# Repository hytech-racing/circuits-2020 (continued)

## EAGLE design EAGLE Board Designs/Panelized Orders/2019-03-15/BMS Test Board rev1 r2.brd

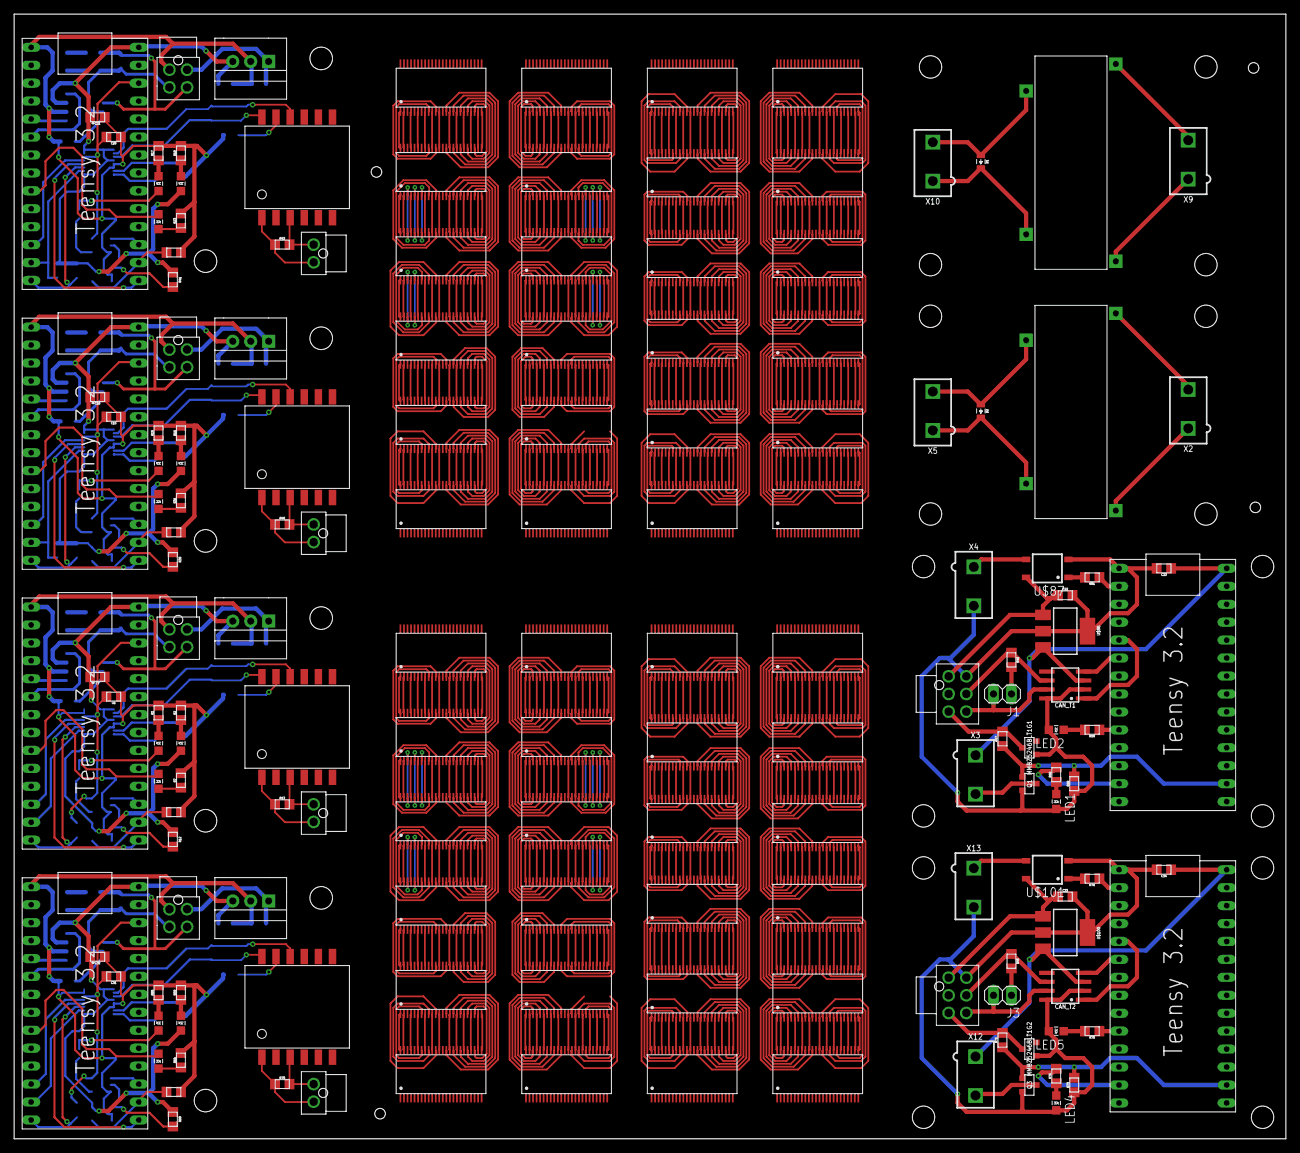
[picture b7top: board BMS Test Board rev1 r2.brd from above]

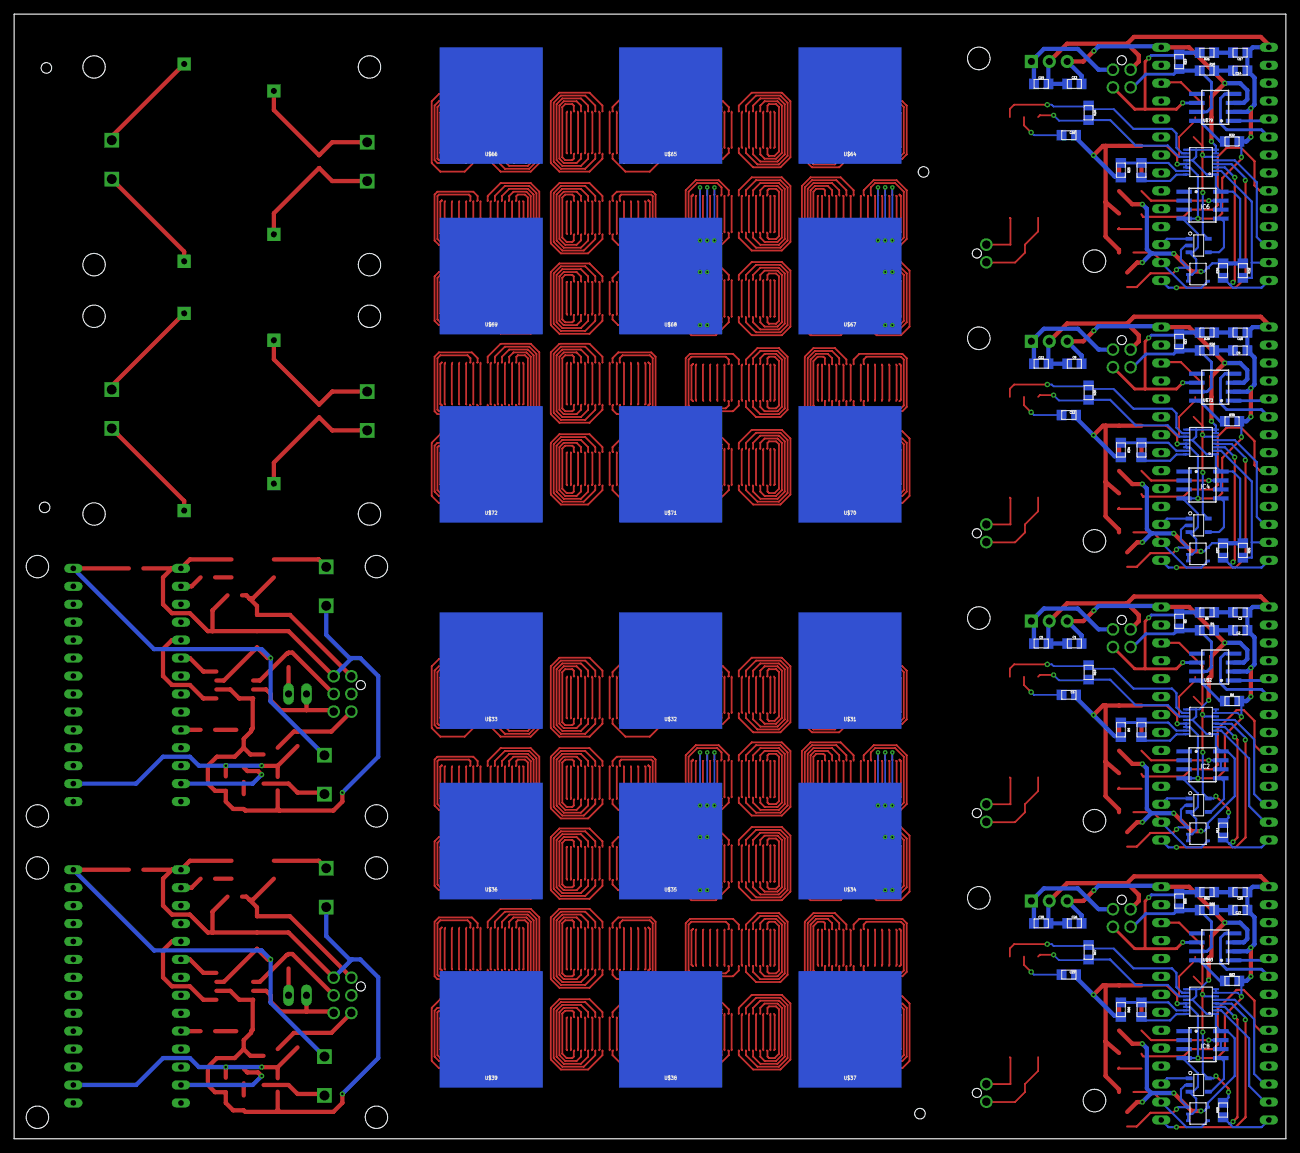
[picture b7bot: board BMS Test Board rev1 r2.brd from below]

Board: 2 copper layers, 180.1 x 159.3 mm, 252 parts (92 on the bottom side), 1128 nets.

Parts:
BMS-OK, BMS-OK1, BMS-OK2, BMS-OK3: GREEN; LED-805
C1, C5, C8, C12, C13, C19, C26, C30: 10uF; 0805
C2, C3, C9, C10, C14, C17, C27, C28: 560pF; 0805
C4, C11, C18, C29: 27pF; 0805
C6, C7, C15, C16, C20, C21, C31, C32: 0.1uF; 0805
C22, C23, C33, C34: 0.22uF; 0805
CAN_T1, CAN_T2: MCP2551; SOIC-08
D1, D2: DIODE0805; 0805_D
IC1, IC3, IC5, IC7: OKI-78SR-5; OKI-78SR
IC2, IC4, IC6, IC8: NE5532SOIC; SOIC-08
ISO_SPI, ISO_SPI1, ISO_SPI2, ISO_SPI3: ISO_SPI; NANO-FIT_VERTICAL-2
J1, J3: JUMPER.1; 1X02
LED1, LED2, LED4, LED5: LED-805
MMBZ5246BLT1G1, MMBZ5246BLT1G2: DIODE_ZENER; SOT23
ON-LED, ON-LED1, ON-LED2, ON-LED3: PURPLE; LED-805
POWER, POWER1, POWER2, POWER3: POWER; NANO-FIT_VERTICAL-4
Q1, Q3: SOT23
R1, R15, R17, R58: 820; 0805
R2, R16, R18, R59: 270; 0805
R3, R10, R19, R26, R27, R35, R45, R46, R60, R67: 120; 0805
R4, R5, R13, R20, R21, R28, R29, R40, R43, R61, R62, R70: 100; 0805
R6, R8, R9, R22, R24, R25, R30, R33, R34, R63, R65, R66: 1k; 0805
R7, R12, R23, R31, R38, R41, R64, R69: 430; 0805
R11, R32, R36, R37, R39, R68: 2k; 0805
R14, R42, R44, R48, R71, R73: 10k; 0805
R47, R72: 20k; 0805
R49, R50, R74, R75: 1.2k; 0805
R51, R76: 330; 0805
TEENSY, TEENSY1, TEENSY2, TEENSY3: BLUE; LED-805
U$1, U$4, U$5, U$6, U$11, U$12, U$13, U$14, U$15, U$16, U$17, U$18, U$19, U$20, U$21, U$22, U$23, U$24, U$25, U$26, U$27, U$28, U$29, U$30, U$40, U$41, U$42, U$43, U$44, U$45, U$46, U$47, U$48, U$49, U$50, U$51, U$52, U$53, U$54, U$55, U$56, U$57, U$58, U$59, U$60, U$61, U$62, U$63: LTC6804-2; LTC6804
U$2, U$73, U$79, U$93: MCP2551; SOIC-08
U$3, U$74, U$80, U$94: LTC6820; MSOP-16
U$7, U$75, U$81, U$85, U$95, U$99: TEENSY_3.2_SIMPLE
U$8, U$76, U$82, U$96: STWD100; SOT23-5
U$9, U$77, U$83, U$97: HM2102NLT
U$10, U$78, U$84, U$98: SN74LVC1G08; SOT-23-5
U$31, U$32, U$33, U$34, U$35, U$36, U$37, U$38, U$39, U$64, U$65, U$66, U$67, U$68, U$69, U$70, U$71, U$72: BATTERY_SPRING_KEYSTONE5222; KEYSTONE5222
U$86, U$100: SOT223
U$87, U$101: CPC1002N; SOP04
U$88, U$92: KT12-1A-40L-THT
X1, X11: CONNECTOR-6NANO-FIT_VERTICAL-6; NANO-FIT_VERTICAL-6
X2, X3, X4, X5, X9, X10, X12, X13: CONNECTOR-2; MINIFIT_5566-2

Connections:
5V2: C34.1, CAN_T2.3, U$99.VIN, U$100.3, X12.1
5V4: C23.1, CAN_T1.3, U$85.VIN, U$86.3, X3.1
12V1: D2.C, U$88.C1, X5.1
12V2: C22.1, U$86.1, U$87.4, X1.P$1
12V3: D1.C, U$92.C1, X10.1
12V4: C33.1, U$100.1, U$101.4, X11.P$1
+3V1: C6.2, R11.1, U$3.6, U$7.3.3V, U$10.5
+3V2: C20.2, U$80.6, U$81.3.3V, U$84.5
+3V3: C15.2, U$74.6, U$75.3.3V, U$78.5
+3V4: C31.2, R68.1, U$94.6, U$95.3.3V, U$98.5
+5V: C8.1, C16.2, IC3.3, IC4.8, ON-LED.A, R36.1, R37.1, R38.1, U$73.3, U$74.1, U$74.7, U$74.8, U$74.9, U$74.12, U$75.VIN, U$76.VCC
+5V1: C1.1, C7.2, IC1.3, IC2.8, ON-LED1.A, R12.1, U$2.3, U$3.1, U$3.9, U$3.12, U$7.VIN, U$8.VCC
+5V2: C13.1, C21.2, IC5.3, IC6.8, ON-LED2.A, R32.1, R39.1, R41.1, U$79.3, U$80.1, U$80.7, U$80.8, U$80.9, U$80.12, U$81.VIN, U$82.VCC
+5V3: C26.1, C32.2, IC7.3, IC8.8, ON-LED3.A, R69.1, U$93.3, U$94.1, U$94.9, U$94.12, U$95.VIN, U$96.VCC
+12V: C12.1, IC3.1, POWER.P$1
+12V1: C5.1, IC1.1, POWER1.P$1
+12V2: C19.1, IC5.1, POWER2.P$1
+12V3: C30.1, IC7.1, POWER3.P$1
BMS_OK: IC4.5, U$78.4
BMS_OK1: IC2.5, U$10.4
BMS_OK2: IC6.5, U$84.4
BMS_OK3: IC8.5, U$98.4
CANH: POWER.P$4, R27.2, R28.2, U$73.7
CANH1: POWER1.P$4, R3.2, R4.2, U$2.7
CANH2: POWER2.P$4, R19.2, R20.2, U$79.7
CANH3: CAN_T1.7, J1.2, X1.P$6
CANH5: POWER3.P$4, R60.2, R61.2, U$93.7
CANH6: CAN_T2.7, J3.2, X11.P$6
CANL: POWER.P$3, R27.1, R29.2, U$73.6
CANL1: POWER1.P$3, R3.1, R5.2, U$2.6
CANL2: POWER2.P$3, R19.1, R21.2, U$79.6
CANL3: CAN_T1.6, R46.1, X1.P$5
CANL5: POWER3.P$3, R60.1, R62.2, U$93.6
CANL6: CAN_T2.6, R45.1, X11.P$5
CANRX1: CAN_T1.4, U$85.D4(CANRX)
CANRX2: CAN_T2.4, U$99.D4(CANRX)
CANTX1: CAN_T1.1, U$85.D3(CANTX)
CANTX2: CAN_T2.1, U$99.D3(CANTX)
CHARGE_ENABLE1: MMBZ5246BLT1G1.3, R47.2, X1.P$3
CHARGE_ENABLE2: MMBZ5246BLT1G2.3, R72.2, X11.P$3
CHRG_C1: R51.1, U$85.D0(RX1)
CHRG_C2: R76.1, U$99.D0(RX1)
CS_LTC1: U$3.5, U$7.D10(TX2)
CS_LTC2: U$80.5, U$81.D10(TX2)
CS_LTC3: U$94.5, U$95.D10(TX2)
CS_LTC6820: U$74.5, U$75.D10(TX2)
GND: C8.2, C9.1, C10.1, C11.2, C12.2, C15.1, C16.1, IC3.2, IC4.4, POWER.P$2, R15.2, R16.2, R30.1, R31.2, R34.2, R42.2, U$73.2, U$74.13, U$74.14, U$75.GND, U$76.EN, U$76.GND, U$78.3
GND1: C1.2, C2.1, C3.1, C4.2, C5.2, C6.1, C7.1, IC1.2, IC2.4, POWER1.P$2, R1.2, R2.2, R6.1, R7.2, R9.2, R14.2, U$2.2, U$3.7, U$3.8, U$3.13, U$3.14, U$7.GND, U$8.EN, U$8.GND, U$10.3
GND2: C13.2, C14.1, C17.1, C18.2, C19.2, C20.1, C21.1, IC5.2, IC6.4, POWER2.P$2, R17.2, R18.2, R22.1, R23.2, R25.2, R44.2, U$79.2, U$80.13, U$80.14, U$81.GND, U$82.EN, U$82.GND, U$84.3
GND3: C22.2, C23.2, CAN_T1.2, CAN_T1.8, LED1.C, LED2.C, MMBZ5246BLT1G1.1, Q1.2, R48.1, U$85.GND, U$86.2, U$86.4, U$87.2, X1.P$4, X4.2
GND4: D2.A, U$88.C2, X5.2
GND6: D1.A, U$92.C2, X10.2
GND7: C26.2, C27.1, C28.1, C29.2, C30.2, C31.1, C32.1, IC7.2, IC8.4, POWER3.P$2, R58.2, R59.2, R63.1, R64.2, R66.2, R71.2, U$93.2, U$94.7, U$94.8, U$94.13, U$94.14, U$95.GND, U$96.EN, U$96.GND, U$98.3
GND8: C33.2, C34.2, CAN_T2.2, CAN_T2.8, LED4.C, LED5.C, MMBZ5246BLT1G2.1, Q3.2, R73.1, U$99.GND, U$100.2, U$100.4, U$101.2, X11.P$4, X13.2
IM: R35.1, U$74.10, U$77.P$10
IM1: R10.1, U$3.10, U$9.P$10
IM2: R26.1, U$80.10, U$83.P$10
IM3: R67.1, U$94.10, U$97.P$10
IP: R35.2, U$74.11, U$77.P$12
IP1: R10.2, U$3.11, U$9.P$12
IP2: R26.2, U$80.11, U$83.P$12
IP3: R67.2, U$94.11, U$97.P$12
ISOSPI-M: ISO_SPI.P$2, R40.2, U$77.P$3
ISOSPI-M1: ISO_SPI1.P$2, R13.2, U$9.P$3
ISOSPI-M2: ISO_SPI2.P$2, R43.2, U$83.P$3
ISOSPI-M3: ISO_SPI3.P$2, R70.2, U$97.P$3
ISOSPI-P: ISO_SPI.P$1, R40.1, U$77.P$1
ISOSPI-P1: ISO_SPI1.P$1, R13.1, U$9.P$1
ISOSPI-P2: ISO_SPI2.P$1, R43.1, U$83.P$1
ISOSPI-P3: ISO_SPI3.P$1, R70.1, U$97.P$1
MISO: R37.2, U$74.3, U$75.D12
MISO1: R11.2, U$3.3, U$7.D12
MISO2: R39.2, U$80.3, U$81.D12
MISO3: R68.2, U$94.3, U$95.D12
MOSI_TEENSY: R36.2, U$74.2, U$75.D11
MOSI_TEENSY1: U$3.2, U$7.D11
MOSI_TEENSY2: R32.2, U$80.2, U$81.D11
MOSI_TEENSY3: U$94.2, U$95.D11
unnamed: U$1.48, U$4.1
unnamed: U$1.47, U$4.2
unnamed: U$1.46, U$4.3
unnamed: U$1.45, U$4.4
unnamed: U$1.44, U$4.5
unnamed: U$1.43, U$4.6
unnamed: U$1.42, U$4.7
unnamed: U$1.41, U$4.8
unnamed: U$1.40, U$4.9
unnamed: U$1.39, U$4.10
unnamed: U$1.38, U$4.11
unnamed: U$1.37, U$4.12
unnamed: U$1.36, U$4.13
unnamed: U$1.35, U$4.14
unnamed: U$1.34, U$4.15
unnamed: U$1.33, U$4.16
unnamed: U$1.32, U$4.17
unnamed: U$1.31, U$4.18
unnamed: U$1.30, U$4.19
unnamed: U$1.29, U$4.20
unnamed: U$1.28, U$4.21
unnamed: U$1.27, U$4.22
unnamed: U$1.26, U$4.23
unnamed: BMS-OK1.A, IC2.6, IC2.7
unnamed: BMS-OK1.C, R1.1
unnamed: ON-LED1.C, R2.1
unnamed: U$2.1, U$7.D3(CANTX)
unnamed: R6.2, U$2.8
unnamed: U$1.25, U$4.24
unnamed: C2.2, R4.1
unnamed: C3.2, R5.1
unnamed: U$4.48, U$5.1
unnamed: U$4.47, U$5.2
unnamed: R7.1, TEENSY1.C
unnamed: R8.1, U$3.16
unnamed: R8.2, R9.1, U$3.15
unnamed: C4.1, U$9.P$11
unnamed: U$4.46, U$5.3
unnamed: U$2.4, U$7.D4(CANRX)
unnamed: U$4.45, U$5.4
unnamed: U$4.44, U$5.5
unnamed: TEENSY1.A, U$7.D7(RX3)
unnamed: R12.2, U$8.WDO, U$10.2
unnamed: U$4.43, U$5.6
unnamed: U$4.42, U$5.7
unnamed: U$4.41, U$5.8
unnamed: U$4.40, U$5.9
unnamed: U$4.39, U$5.10
unnamed: U$7.A1, U$10.1
unnamed: U$4.38, U$5.11
unnamed: U$4.37, U$5.12
unnamed: U$4.36, U$5.13
unnamed: U$4.35, U$5.14
unnamed: U$4.34, U$5.15
unnamed: U$4.33, U$5.16
unnamed: U$4.32, U$5.17
unnamed: U$4.31, U$5.18
unnamed: U$4.30, U$5.19
unnamed: U$4.29, U$5.20
unnamed: U$4.28, U$5.21
unnamed: U$4.27, U$5.22
unnamed: U$4.26, U$5.23
unnamed: U$4.25, U$5.24
unnamed: U$5.48, U$6.1
unnamed: U$5.47, U$6.2
unnamed: U$5.46, U$6.3
unnamed: U$5.45, U$6.4
unnamed: U$5.44, U$6.5
unnamed: U$5.43, U$6.6
unnamed: U$5.42, U$6.7
unnamed: U$5.41, U$6.8
unnamed: U$5.40, U$6.9
unnamed: U$5.39, U$6.10
unnamed: U$5.38, U$6.11
unnamed: U$5.37, U$6.12
unnamed: U$5.36, U$6.13
unnamed: U$5.35, U$6.14
unnamed: U$5.34, U$6.15
unnamed: U$5.33, U$6.16
unnamed: U$5.32, U$6.17
unnamed: U$5.31, U$6.18
unnamed: U$5.30, U$6.19
unnamed: U$5.29, U$6.20
unnamed: U$5.28, U$6.21
unnamed: U$5.27, U$6.22
unnamed: U$5.26, U$6.23
unnamed: U$5.25, U$6.24
unnamed: U$6.48, U$11.1
unnamed: U$6.47, U$11.2
unnamed: U$6.46, U$11.3
unnamed: U$6.45, U$11.4
unnamed: U$6.44, U$11.5
unnamed: U$6.43, U$11.6
unnamed: U$6.42, U$11.7
unnamed: U$6.41, U$11.8
unnamed: U$6.40, U$11.9
unnamed: U$6.39, U$11.10
unnamed: U$6.38, U$11.11
unnamed: U$6.37, U$11.12
unnamed: U$6.36, U$11.13
unnamed: U$6.35, U$11.14
unnamed: U$6.34, U$11.15
unnamed: U$6.33, U$11.16
unnamed: U$6.32, U$11.17
unnamed: U$6.31, U$11.18
unnamed: U$6.30, U$11.19
unnamed: U$6.29, U$11.20
unnamed: U$6.28, U$11.21
unnamed: U$6.27, U$11.22
unnamed: U$6.26, U$11.23
unnamed: U$6.25, U$11.24
unnamed: U$11.48, U$12.1
unnamed: U$11.47, U$12.2
unnamed: U$11.46, U$12.3
unnamed: U$11.45, U$12.4
unnamed: U$11.44, U$12.5
unnamed: U$11.43, U$12.6
unnamed: U$11.42, U$12.7
unnamed: U$11.41, U$12.8
unnamed: U$11.40, U$12.9
unnamed: U$11.39, U$12.10
unnamed: U$11.38, U$12.11
unnamed: U$11.37, U$12.12
unnamed: U$11.36, U$12.13
unnamed: U$11.35, U$12.14
unnamed: U$11.34, U$12.15
unnamed: U$11.33, U$12.16
unnamed: U$11.32, U$12.17
unnamed: U$11.31, U$12.18
unnamed: U$11.30, U$12.19
unnamed: U$11.29, U$12.20
unnamed: U$11.28, U$12.21
unnamed: U$11.27, U$12.22
unnamed: U$11.26, U$12.23
unnamed: U$11.25, U$12.24
unnamed: U$13.25, U$14.24
unnamed: U$13.26, U$14.23
unnamed: U$13.27, U$14.22
unnamed: U$13.28, U$14.21
unnamed: U$13.29, U$14.20
unnamed: U$13.30, U$14.19
unnamed: U$13.31, U$14.18
unnamed: U$13.32, U$14.17
unnamed: U$13.33, U$14.16
unnamed: U$13.34, U$14.15
unnamed: U$13.35, U$14.14
unnamed: U$13.36, U$14.13
unnamed: U$13.37, U$14.12
unnamed: U$13.38, U$14.11
unnamed: U$13.39, U$14.10
unnamed: U$13.40, U$14.9
unnamed: U$13.41, U$14.8
unnamed: U$13.42, U$14.7
unnamed: U$13.43, U$14.6
unnamed: U$13.44, U$14.5
unnamed: U$13.45, U$14.4
unnamed: U$13.46, U$14.3
unnamed: U$13.47, U$14.2
unnamed: U$13.48, U$14.1
unnamed: U$14.25, U$15.24
unnamed: U$14.26, U$15.23
unnamed: U$14.27, U$15.22
unnamed: U$14.28, U$15.21
unnamed: U$14.29, U$15.20
unnamed: U$14.30, U$15.19
unnamed: U$14.31, U$15.18
unnamed: U$14.32, U$15.17
unnamed: U$14.33, U$15.16
unnamed: U$14.34, U$15.15
unnamed: U$14.35, U$15.14
unnamed: U$14.36, U$15.13
unnamed: U$14.37, U$15.12
unnamed: U$14.38, U$15.11
unnamed: U$14.39, U$15.10
unnamed: U$14.40, U$15.9
unnamed: U$14.41, U$15.8
unnamed: U$14.42, U$15.7
unnamed: U$14.43, U$15.6
unnamed: U$14.44, U$15.5
unnamed: U$14.45, U$15.4
unnamed: U$14.46, U$15.3
unnamed: U$14.47, U$15.2
unnamed: U$14.48, U$15.1
unnamed: U$15.25, U$16.24
unnamed: U$15.26, U$16.23
unnamed: U$15.27, U$16.22
unnamed: U$15.28, U$16.21
unnamed: U$15.29, U$16.20
unnamed: U$15.30, U$16.19
unnamed: U$15.31, U$16.18
unnamed: U$15.32, U$16.17
unnamed: U$15.33, U$16.16
unnamed: U$15.34, U$16.15
unnamed: U$15.35, U$16.14
unnamed: U$15.36, U$16.13
unnamed: U$15.37, U$16.12
unnamed: U$15.38, U$16.11
unnamed: U$15.39, U$16.10
unnamed: U$15.40, U$16.9
unnamed: U$15.41, U$16.8
unnamed: U$15.42, U$16.7
unnamed: U$15.43, U$16.6
unnamed: U$15.44, U$16.5
unnamed: U$15.45, U$16.4
unnamed: U$15.46, U$16.3
unnamed: U$15.47, U$16.2
unnamed: U$15.48, U$16.1
unnamed: U$16.25, U$17.24
unnamed: U$16.26, U$17.23
unnamed: U$16.27, U$17.22
unnamed: U$16.28, U$17.21
unnamed: U$16.29, U$17.20
unnamed: U$16.30, U$17.19
unnamed: U$16.31, U$17.18
unnamed: U$16.32, U$17.17
unnamed: U$16.33, U$17.16
unnamed: U$16.34, U$17.15
unnamed: U$16.35, U$17.14
unnamed: U$16.36, U$17.13
unnamed: U$16.37, U$17.12
unnamed: U$16.38, U$17.11
unnamed: U$16.39, U$17.10
unnamed: U$16.40, U$17.9
unnamed: U$16.41, U$17.8
unnamed: U$16.42, U$17.7
unnamed: U$16.43, U$17.6
unnamed: U$16.44, U$17.5
unnamed: U$16.45, U$17.4
unnamed: U$16.46, U$17.3
unnamed: U$16.47, U$17.2
unnamed: U$16.48, U$17.1
unnamed: U$17.25, U$18.24
unnamed: U$17.26, U$18.23
unnamed: U$17.27, U$18.22
unnamed: U$17.28, U$18.21
unnamed: U$17.29, U$18.20
unnamed: U$17.30, U$18.19
unnamed: U$17.31, U$18.18
unnamed: U$17.32, U$18.17
unnamed: U$17.33, U$18.16
unnamed: U$17.34, U$18.15
unnamed: U$17.35, U$18.14
unnamed: U$17.36, U$18.13
unnamed: U$17.37, U$18.12
unnamed: U$17.38, U$18.11
unnamed: U$17.39, U$18.10
unnamed: U$17.40, U$18.9
unnamed: U$17.41, U$18.8
unnamed: U$17.42, U$18.7
unnamed: U$17.43, U$18.6
unnamed: U$17.44, U$18.5
unnamed: U$17.45, U$18.4
unnamed: U$17.46, U$18.3
unnamed: U$17.47, U$18.2
unnamed: U$17.48, U$18.1
unnamed: U$19.48, U$20.1
unnamed: U$19.47, U$20.2
unnamed: U$19.46, U$20.3
unnamed: U$19.45, U$20.4
unnamed: U$19.44, U$20.5
unnamed: U$19.43, U$20.6
unnamed: U$19.42, U$20.7
unnamed: U$19.41, U$20.8
unnamed: U$19.40, U$20.9
unnamed: U$19.39, U$20.10
unnamed: U$19.38, U$20.11
unnamed: U$19.37, U$20.12
unnamed: U$19.36, U$20.13
unnamed: U$19.35, U$20.14
unnamed: U$19.34, U$20.15
unnamed: U$19.33, U$20.16
unnamed: U$19.32, U$20.17
unnamed: U$19.31, U$20.18
unnamed: U$19.30, U$20.19
unnamed: U$19.29, U$20.20
unnamed: U$19.28, U$20.21
unnamed: U$19.27, U$20.22
unnamed: U$19.26, U$20.23
unnamed: U$19.25, U$20.24
unnamed: U$20.48, U$21.1
unnamed: U$20.47, U$21.2
unnamed: U$20.46, U$21.3
unnamed: U$20.45, U$21.4
unnamed: U$20.44, U$21.5
unnamed: U$20.43, U$21.6
unnamed: U$20.42, U$21.7
unnamed: U$20.41, U$21.8
unnamed: U$20.40, U$21.9
unnamed: U$20.39, U$21.10
unnamed: U$20.38, U$21.11
unnamed: U$20.37, U$21.12
unnamed: U$20.36, U$21.13
unnamed: U$20.35, U$21.14
unnamed: U$20.34, U$21.15
unnamed: U$20.33, U$21.16
unnamed: U$20.32, U$21.17
unnamed: U$20.31, U$21.18
unnamed: U$20.30, U$21.19
unnamed: U$20.29, U$21.20
unnamed: U$20.28, U$21.21
unnamed: U$20.27, U$21.22
unnamed: U$20.26, U$21.23
unnamed: U$20.25, U$21.24
unnamed: U$21.48, U$22.1
unnamed: U$21.47, U$22.2
unnamed: U$21.46, U$22.3
unnamed: U$21.45, U$22.4
unnamed: U$21.44, U$22.5
unnamed: U$21.43, U$22.6
unnamed: U$21.42, U$22.7
unnamed: U$21.41, U$22.8
unnamed: U$21.40, U$22.9
unnamed: U$21.39, U$22.10
unnamed: U$21.38, U$22.11
unnamed: U$21.37, U$22.12
unnamed: U$21.36, U$22.13
unnamed: U$21.35, U$22.14
unnamed: U$21.34, U$22.15
unnamed: U$21.33, U$22.16
unnamed: U$21.32, U$22.17
unnamed: U$21.31, U$22.18
unnamed: U$21.30, U$22.19
unnamed: U$21.29, U$22.20
unnamed: U$21.28, U$22.21
unnamed: U$21.27, U$22.22
unnamed: U$21.26, U$22.23
unnamed: U$21.25, U$22.24
unnamed: U$22.48, U$23.1
unnamed: U$22.47, U$23.2
unnamed: U$22.46, U$23.3
unnamed: U$22.45, U$23.4
unnamed: U$22.44, U$23.5
unnamed: U$22.43, U$23.6
unnamed: U$22.42, U$23.7
unnamed: U$22.41, U$23.8
unnamed: U$22.40, U$23.9
unnamed: U$22.39, U$23.10
unnamed: U$22.38, U$23.11
unnamed: U$22.37, U$23.12
unnamed: U$22.36, U$23.13
unnamed: U$22.35, U$23.14
unnamed: U$22.34, U$23.15
unnamed: U$22.33, U$23.16
unnamed: U$22.32, U$23.17
unnamed: U$22.31, U$23.18
unnamed: U$22.30, U$23.19
unnamed: U$22.29, U$23.20
unnamed: U$22.28, U$23.21
unnamed: U$22.27, U$23.22
unnamed: U$22.26, U$23.23
unnamed: U$22.25, U$23.24
unnamed: U$23.48, U$24.1
unnamed: U$23.47, U$24.2
unnamed: U$23.46, U$24.3
unnamed: U$23.45, U$24.4
unnamed: U$23.44, U$24.5
unnamed: U$23.43, U$24.6
unnamed: U$23.42, U$24.7
unnamed: U$23.41, U$24.8
unnamed: U$23.40, U$24.9
unnamed: U$23.39, U$24.10
unnamed: U$23.38, U$24.11
unnamed: U$23.37, U$24.12
unnamed: U$23.36, U$24.13
unnamed: U$23.35, U$24.14
unnamed: U$23.34, U$24.15
unnamed: U$23.33, U$24.16
unnamed: U$23.32, U$24.17
unnamed: U$23.31, U$24.18
unnamed: U$23.30, U$24.19
unnamed: U$23.29, U$24.20
unnamed: U$23.28, U$24.21
unnamed: U$23.27, U$24.22
unnamed: U$23.26, U$24.23
unnamed: U$23.25, U$24.24
unnamed: U$25.25, U$26.24
unnamed: U$25.26, U$26.23
unnamed: U$25.27, U$26.22
unnamed: U$25.28, U$26.21
unnamed: U$25.29, U$26.20
unnamed: U$25.30, U$26.19
unnamed: U$25.31, U$26.18
unnamed: U$25.32, U$26.17
unnamed: U$25.33, U$26.16
unnamed: U$25.34, U$26.15
unnamed: U$25.35, U$26.14
unnamed: U$25.36, U$26.13
unnamed: U$25.37, U$26.12
unnamed: U$25.38, U$26.11
unnamed: U$25.39, U$26.10
unnamed: U$25.40, U$26.9
unnamed: U$25.41, U$26.8
unnamed: U$25.42, U$26.7
unnamed: U$25.43, U$26.6
unnamed: U$25.44, U$26.5
unnamed: U$25.45, U$26.4
unnamed: U$25.46, U$26.3
unnamed: U$25.47, U$26.2
unnamed: U$25.48, U$26.1
unnamed: U$26.25, U$27.24
unnamed: U$26.26, U$27.23
unnamed: U$26.27, U$27.22
unnamed: U$26.28, U$27.21
unnamed: U$26.29, U$27.20
unnamed: U$26.30, U$27.19
unnamed: U$26.31, U$27.18
unnamed: U$26.32, U$27.17
unnamed: U$26.33, U$27.16
unnamed: U$26.34, U$27.15
unnamed: U$26.35, U$27.14
unnamed: U$26.36, U$27.13
unnamed: U$26.37, U$27.12
unnamed: U$26.38, U$27.11
unnamed: U$26.39, U$27.10
unnamed: U$26.40, U$27.9
unnamed: U$26.41, U$27.8
unnamed: U$26.42, U$27.7
unnamed: U$26.43, U$27.6
unnamed: U$26.44, U$27.5
unnamed: U$26.45, U$27.4
unnamed: U$26.46, U$27.3
unnamed: U$26.47, U$27.2
unnamed: U$26.48, U$27.1
unnamed: U$27.25, U$28.24
unnamed: U$27.26, U$28.23
unnamed: U$27.27, U$28.22
unnamed: U$27.28, U$28.21
unnamed: U$27.29, U$28.20
unnamed: U$27.30, U$28.19
unnamed: U$27.31, U$28.18
unnamed: U$27.32, U$28.17
unnamed: U$27.33, U$28.16
unnamed: U$27.34, U$28.15
unnamed: U$27.35, U$28.14
unnamed: U$27.36, U$28.13
unnamed: U$27.37, U$28.12
unnamed: U$27.38, U$28.11
unnamed: U$27.39, U$28.10
unnamed: U$27.40, U$28.9
unnamed: U$27.41, U$28.8
unnamed: U$27.42, U$28.7
unnamed: U$27.43, U$28.6
unnamed: U$27.44, U$28.5
unnamed: U$27.45, U$28.4
unnamed: U$27.46, U$28.3
unnamed: U$27.47, U$28.2
unnamed: U$27.48, U$28.1
unnamed: U$28.25, U$29.24
unnamed: U$28.26, U$29.23
unnamed: U$28.27, U$29.22
unnamed: U$28.28, U$29.21
unnamed: U$28.29, U$29.20
unnamed: U$28.30, U$29.19
unnamed: U$28.31, U$29.18
unnamed: U$28.32, U$29.17
unnamed: U$28.33, U$29.16
unnamed: U$28.34, U$29.15
unnamed: U$28.35, U$29.14
unnamed: U$28.36, U$29.13
unnamed: U$28.37, U$29.12
unnamed: U$28.38, U$29.11
unnamed: U$28.39, U$29.10
unnamed: U$28.40, U$29.9
unnamed: U$28.41, U$29.8
unnamed: U$28.42, U$29.7
unnamed: U$28.43, U$29.6
unnamed: U$28.44, U$29.5
unnamed: U$28.45, U$29.4
unnamed: U$28.46, U$29.3
unnamed: U$28.47, U$29.2
unnamed: U$28.48, U$29.1
unnamed: U$29.25, U$30.24
unnamed: U$29.26, U$30.23
unnamed: U$29.27, U$30.22
unnamed: U$29.28, U$30.21
unnamed: U$29.29, U$30.20
unnamed: U$29.30, U$30.19
unnamed: U$29.31, U$30.18
unnamed: U$29.32, U$30.17
unnamed: U$29.33, U$30.16
unnamed: U$29.34, U$30.15
unnamed: U$29.35, U$30.14
unnamed: U$29.36, U$30.13
unnamed: U$29.37, U$30.12
unnamed: U$29.38, U$30.11
unnamed: U$29.39, U$30.10
unnamed: U$29.40, U$30.9
unnamed: U$29.41, U$30.8
unnamed: U$29.42, U$30.7
unnamed: U$29.43, U$30.6
unnamed: U$29.44, U$30.5
unnamed: U$29.45, U$30.4
unnamed: U$29.46, U$30.3
unnamed: U$29.47, U$30.2
unnamed: U$29.48, U$30.1
unnamed: U$40.48, U$41.1
unnamed: U$40.47, U$41.2
unnamed: U$40.46, U$41.3
unnamed: U$40.45, U$41.4
unnamed: U$40.44, U$41.5
unnamed: U$40.43, U$41.6
unnamed: U$40.42, U$41.7
unnamed: U$40.41, U$41.8
unnamed: U$40.40, U$41.9
unnamed: U$40.39, U$41.10
unnamed: U$40.38, U$41.11
unnamed: U$40.37, U$41.12
unnamed: U$40.36, U$41.13
unnamed: U$40.35, U$41.14
unnamed: U$40.34, U$41.15
unnamed: U$40.33, U$41.16
unnamed: U$40.32, U$41.17
unnamed: U$40.31, U$41.18
unnamed: U$40.30, U$41.19
unnamed: U$40.29, U$41.20
unnamed: U$40.28, U$41.21
unnamed: U$40.27, U$41.22
unnamed: U$40.26, U$41.23
unnamed: U$40.25, U$41.24
unnamed: U$41.48, U$42.1
unnamed: U$41.47, U$42.2
unnamed: U$41.46, U$42.3
unnamed: U$41.45, U$42.4
unnamed: U$41.44, U$42.5
unnamed: U$41.43, U$42.6
unnamed: U$41.42, U$42.7
unnamed: U$41.41, U$42.8
unnamed: U$41.40, U$42.9
unnamed: U$41.39, U$42.10
unnamed: U$41.38, U$42.11
unnamed: U$41.37, U$42.12
unnamed: U$41.36, U$42.13
unnamed: U$41.35, U$42.14
unnamed: U$41.34, U$42.15
unnamed: U$41.33, U$42.16
unnamed: U$41.32, U$42.17
unnamed: U$41.31, U$42.18
unnamed: U$41.30, U$42.19
unnamed: U$41.29, U$42.20
unnamed: U$41.28, U$42.21
unnamed: U$41.27, U$42.22
unnamed: U$41.26, U$42.23
unnamed: U$41.25, U$42.24
unnamed: U$42.48, U$43.1
unnamed: U$42.47, U$43.2
unnamed: U$42.46, U$43.3
unnamed: U$42.45, U$43.4
unnamed: U$42.44, U$43.5
unnamed: U$42.43, U$43.6
unnamed: U$42.42, U$43.7
unnamed: U$42.41, U$43.8
unnamed: U$42.40, U$43.9
unnamed: U$42.39, U$43.10
unnamed: U$42.38, U$43.11
unnamed: U$42.37, U$43.12
unnamed: U$42.36, U$43.13
unnamed: U$42.35, U$43.14
unnamed: U$42.34, U$43.15
unnamed: U$42.33, U$43.16
unnamed: U$42.32, U$43.17
unnamed: U$42.31, U$43.18
unnamed: U$42.30, U$43.19
unnamed: U$42.29, U$43.20
unnamed: U$42.28, U$43.21
unnamed: U$42.27, U$43.22
unnamed: U$42.26, U$43.23
unnamed: U$42.25, U$43.24
unnamed: U$43.48, U$44.1
unnamed: U$43.47, U$44.2
unnamed: U$43.46, U$44.3
unnamed: U$43.45, U$44.4
unnamed: U$43.44, U$44.5
unnamed: U$43.43, U$44.6
unnamed: U$43.42, U$44.7
unnamed: U$43.41, U$44.8
unnamed: U$43.40, U$44.9
unnamed: U$43.39, U$44.10
unnamed: U$43.38, U$44.11
unnamed: U$43.37, U$44.12
unnamed: U$43.36, U$44.13
unnamed: U$43.35, U$44.14
unnamed: U$43.34, U$44.15
unnamed: U$43.33, U$44.16
unnamed: U$43.32, U$44.17
unnamed: U$43.31, U$44.18
unnamed: U$43.30, U$44.19
unnamed: U$43.29, U$44.20
unnamed: U$43.28, U$44.21
unnamed: U$43.27, U$44.22
unnamed: U$43.26, U$44.23
unnamed: U$43.25, U$44.24
unnamed: U$44.48, U$45.1
unnamed: U$44.47, U$45.2
unnamed: U$44.46, U$45.3
unnamed: U$44.45, U$45.4
unnamed: U$44.44, U$45.5
unnamed: U$44.43, U$45.6
unnamed: U$44.42, U$45.7
unnamed: U$44.41, U$45.8
unnamed: U$44.40, U$45.9
unnamed: U$44.39, U$45.10
unnamed: U$44.38, U$45.11
unnamed: U$44.37, U$45.12
unnamed: U$44.36, U$45.13
unnamed: U$44.35, U$45.14
unnamed: U$44.34, U$45.15
unnamed: U$44.33, U$45.16
unnamed: U$44.32, U$45.17
unnamed: U$44.31, U$45.18
unnamed: U$44.30, U$45.19
unnamed: U$44.29, U$45.20
unnamed: U$44.28, U$45.21
unnamed: U$44.27, U$45.22
unnamed: U$44.26, U$45.23
unnamed: U$44.25, U$45.24
unnamed: U$46.25, U$47.24
unnamed: U$46.26, U$47.23
unnamed: U$46.27, U$47.22
unnamed: U$46.28, U$47.21
unnamed: U$46.29, U$47.20
unnamed: U$46.30, U$47.19
unnamed: U$46.31, U$47.18
unnamed: U$46.32, U$47.17
unnamed: U$46.33, U$47.16
unnamed: U$46.34, U$47.15
unnamed: U$46.35, U$47.14
unnamed: U$46.36, U$47.13
unnamed: U$46.37, U$47.12
unnamed: U$46.38, U$47.11
unnamed: U$46.39, U$47.10
unnamed: U$46.40, U$47.9
unnamed: U$46.41, U$47.8
unnamed: U$46.42, U$47.7
unnamed: U$46.43, U$47.6
unnamed: U$46.44, U$47.5
unnamed: U$46.45, U$47.4
unnamed: U$46.46, U$47.3
unnamed: U$46.47, U$47.2
unnamed: U$46.48, U$47.1
unnamed: U$47.25, U$48.24
unnamed: U$47.26, U$48.23
unnamed: U$47.27, U$48.22
unnamed: U$47.28, U$48.21
unnamed: U$47.29, U$48.20
unnamed: U$47.30, U$48.19
unnamed: U$47.31, U$48.18
unnamed: U$47.32, U$48.17
unnamed: U$47.33, U$48.16
unnamed: U$47.34, U$48.15
unnamed: U$47.35, U$48.14
unnamed: U$47.36, U$48.13
unnamed: U$47.37, U$48.12
unnamed: U$47.38, U$48.11
unnamed: U$47.39, U$48.10
unnamed: U$47.40, U$48.9
unnamed: U$47.41, U$48.8
unnamed: U$47.42, U$48.7
unnamed: U$47.43, U$48.6
unnamed: U$47.44, U$48.5
unnamed: U$47.45, U$48.4
unnamed: U$47.46, U$48.3
unnamed: U$47.47, U$48.2
unnamed: U$47.48, U$48.1
unnamed: U$48.25, U$49.24
unnamed: U$48.26, U$49.23
unnamed: U$48.27, U$49.22
unnamed: U$48.28, U$49.21
unnamed: U$48.29, U$49.20
unnamed: U$48.30, U$49.19
unnamed: U$48.31, U$49.18
unnamed: U$48.32, U$49.17
unnamed: U$48.33, U$49.16
unnamed: U$48.34, U$49.15
unnamed: U$48.35, U$49.14
unnamed: U$48.36, U$49.13
unnamed: U$48.37, U$49.12
unnamed: U$48.38, U$49.11
unnamed: U$48.39, U$49.10
unnamed: U$48.40, U$49.9
unnamed: U$48.41, U$49.8
unnamed: U$48.42, U$49.7
unnamed: U$48.43, U$49.6
unnamed: U$48.44, U$49.5
unnamed: U$48.45, U$49.4
unnamed: U$48.46, U$49.3
unnamed: U$48.47, U$49.2
unnamed: U$48.48, U$49.1
unnamed: U$49.25, U$50.24
unnamed: U$49.26, U$50.23
unnamed: U$49.27, U$50.22
unnamed: U$49.28, U$50.21
unnamed: U$49.29, U$50.20
unnamed: U$49.30, U$50.19
unnamed: U$49.31, U$50.18
unnamed: U$49.32, U$50.17
unnamed: U$49.33, U$50.16
unnamed: U$49.34, U$50.15
unnamed: U$49.35, U$50.14
unnamed: U$49.36, U$50.13
unnamed: U$49.37, U$50.12
unnamed: U$49.38, U$50.11
unnamed: U$49.39, U$50.10
unnamed: U$49.40, U$50.9
unnamed: U$49.41, U$50.8
unnamed: U$49.42, U$50.7
unnamed: U$49.43, U$50.6
unnamed: U$49.44, U$50.5
unnamed: U$49.45, U$50.4
unnamed: U$49.46, U$50.3
unnamed: U$49.47, U$50.2
unnamed: U$49.48, U$50.1
unnamed: U$50.25, U$51.24
unnamed: U$50.26, U$51.23
unnamed: U$50.27, U$51.22
unnamed: U$50.28, U$51.21
unnamed: U$50.29, U$51.20
unnamed: U$50.30, U$51.19
unnamed: U$50.31, U$51.18
unnamed: U$50.32, U$51.17
unnamed: U$50.33, U$51.16
unnamed: U$50.34, U$51.15
unnamed: U$50.35, U$51.14
unnamed: U$50.36, U$51.13
unnamed: U$50.37, U$51.12
unnamed: U$50.38, U$51.11
unnamed: U$50.39, U$51.10
unnamed: U$50.40, U$51.9
unnamed: U$50.41, U$51.8
unnamed: U$50.42, U$51.7
unnamed: U$50.43, U$51.6
unnamed: U$50.44, U$51.5
unnamed: U$50.45, U$51.4
unnamed: U$50.46, U$51.3
unnamed: U$50.47, U$51.2
unnamed: U$50.48, U$51.1
unnamed: U$52.48, U$53.1
unnamed: U$52.47, U$53.2
unnamed: U$52.46, U$53.3
unnamed: U$52.45, U$53.4
unnamed: U$52.44, U$53.5
unnamed: U$52.43, U$53.6
unnamed: U$52.42, U$53.7
unnamed: U$52.41, U$53.8
unnamed: U$52.40, U$53.9
unnamed: U$52.39, U$53.10
unnamed: U$52.38, U$53.11
unnamed: U$52.37, U$53.12
unnamed: U$52.36, U$53.13
unnamed: U$52.35, U$53.14
unnamed: U$52.34, U$53.15
unnamed: U$52.33, U$53.16
unnamed: U$52.32, U$53.17
unnamed: U$52.31, U$53.18
unnamed: U$52.30, U$53.19
unnamed: U$52.29, U$53.20
unnamed: U$52.28, U$53.21
unnamed: U$52.27, U$53.22
unnamed: U$52.26, U$53.23
unnamed: U$52.25, U$53.24
unnamed: U$53.48, U$54.1
unnamed: U$53.47, U$54.2
unnamed: U$53.46, U$54.3
unnamed: U$53.45, U$54.4
unnamed: U$53.44, U$54.5
unnamed: U$53.43, U$54.6
unnamed: U$53.42, U$54.7
unnamed: U$53.41, U$54.8
unnamed: U$53.40, U$54.9
unnamed: U$53.39, U$54.10
unnamed: U$53.38, U$54.11
unnamed: U$53.37, U$54.12
unnamed: U$53.36, U$54.13
unnamed: U$53.35, U$54.14
unnamed: U$53.34, U$54.15
unnamed: U$53.33, U$54.16
unnamed: U$53.32, U$54.17
unnamed: U$53.31, U$54.18
unnamed: U$53.30, U$54.19
unnamed: U$53.29, U$54.20
unnamed: U$53.28, U$54.21
unnamed: U$53.27, U$54.22
unnamed: U$53.26, U$54.23
unnamed: U$53.25, U$54.24
unnamed: U$54.48, U$55.1
unnamed: U$54.47, U$55.2
unnamed: U$54.46, U$55.3
unnamed: U$54.45, U$55.4
unnamed: U$54.44, U$55.5
unnamed: U$54.43, U$55.6
unnamed: U$54.42, U$55.7
unnamed: U$54.41, U$55.8
unnamed: U$54.40, U$55.9
unnamed: U$54.39, U$55.10
unnamed: U$54.38, U$55.11
unnamed: U$54.37, U$55.12
unnamed: U$54.36, U$55.13
unnamed: U$54.35, U$55.14
unnamed: U$54.34, U$55.15
unnamed: U$54.33, U$55.16
unnamed: U$54.32, U$55.17
unnamed: U$54.31, U$55.18
unnamed: U$54.30, U$55.19
unnamed: U$54.29, U$55.20
unnamed: U$54.28, U$55.21
unnamed: U$54.27, U$55.22
unnamed: U$54.26, U$55.23
unnamed: U$54.25, U$55.24
unnamed: U$55.48, U$56.1
unnamed: U$55.47, U$56.2
unnamed: U$55.46, U$56.3
unnamed: U$55.45, U$56.4
unnamed: U$55.44, U$56.5
unnamed: U$55.43, U$56.6
unnamed: U$55.42, U$56.7
unnamed: U$55.41, U$56.8
unnamed: U$55.40, U$56.9
unnamed: U$55.39, U$56.10
unnamed: U$55.38, U$56.11
unnamed: U$55.37, U$56.12
unnamed: U$55.36, U$56.13
unnamed: U$55.35, U$56.14
unnamed: U$55.34, U$56.15
unnamed: U$55.33, U$56.16
unnamed: U$55.32, U$56.17
unnamed: U$55.31, U$56.18
unnamed: U$55.30, U$56.19
unnamed: U$55.29, U$56.20
unnamed: U$55.28, U$56.21
unnamed: U$55.27, U$56.22
unnamed: U$55.26, U$56.23
unnamed: U$55.25, U$56.24
unnamed: U$56.48, U$57.1
unnamed: U$56.47, U$57.2
unnamed: U$56.46, U$57.3
unnamed: U$56.45, U$57.4
unnamed: U$56.44, U$57.5
unnamed: U$56.43, U$57.6
unnamed: U$56.42, U$57.7
unnamed: U$56.41, U$57.8
unnamed: U$56.40, U$57.9
unnamed: U$56.39, U$57.10
unnamed: U$56.38, U$57.11
unnamed: U$56.37, U$57.12
unnamed: U$56.36, U$57.13
unnamed: U$56.35, U$57.14
unnamed: U$56.34, U$57.15
unnamed: U$56.33, U$57.16
unnamed: U$56.32, U$57.17
unnamed: U$56.31, U$57.18
unnamed: U$56.30, U$57.19
unnamed: U$56.29, U$57.20
unnamed: U$56.28, U$57.21
unnamed: U$56.27, U$57.22
unnamed: U$56.26, U$57.23
unnamed: U$56.25, U$57.24
unnamed: U$58.25, U$59.24
unnamed: U$58.26, U$59.23
unnamed: U$58.27, U$59.22
unnamed: U$58.28, U$59.21
unnamed: U$58.29, U$59.20
unnamed: U$58.30, U$59.19
unnamed: U$58.31, U$59.18
unnamed: U$58.32, U$59.17
unnamed: U$58.33, U$59.16
unnamed: U$58.34, U$59.15
unnamed: U$58.35, U$59.14
unnamed: U$58.36, U$59.13
unnamed: U$58.37, U$59.12
unnamed: U$58.38, U$59.11
unnamed: U$58.39, U$59.10
unnamed: U$58.40, U$59.9
unnamed: U$58.41, U$59.8
unnamed: U$58.42, U$59.7
unnamed: U$58.43, U$59.6
unnamed: U$58.44, U$59.5
unnamed: U$58.45, U$59.4
unnamed: U$58.46, U$59.3
unnamed: U$58.47, U$59.2
unnamed: U$58.48, U$59.1
unnamed: U$59.25, U$60.24
unnamed: U$59.26, U$60.23
unnamed: U$59.27, U$60.22
unnamed: U$59.28, U$60.21
unnamed: U$59.29, U$60.20
unnamed: U$59.30, U$60.19
unnamed: U$59.31, U$60.18
unnamed: U$59.32, U$60.17
unnamed: U$59.33, U$60.16
unnamed: U$59.34, U$60.15
unnamed: U$59.35, U$60.14
unnamed: U$59.36, U$60.13
unnamed: U$59.37, U$60.12
unnamed: U$59.38, U$60.11
unnamed: U$59.39, U$60.10
unnamed: U$59.40, U$60.9
unnamed: U$59.41, U$60.8
unnamed: U$59.42, U$60.7
unnamed: U$59.43, U$60.6
unnamed: U$59.44, U$60.5
unnamed: U$59.45, U$60.4
unnamed: U$59.46, U$60.3
unnamed: U$59.47, U$60.2
unnamed: U$59.48, U$60.1
unnamed: U$60.25, U$61.24
unnamed: U$60.26, U$61.23
unnamed: U$60.27, U$61.22
unnamed: U$60.28, U$61.21
unnamed: U$60.29, U$61.20
unnamed: U$60.30, U$61.19
unnamed: U$60.31, U$61.18
unnamed: U$60.32, U$61.17
unnamed: U$60.33, U$61.16
unnamed: U$60.34, U$61.15
unnamed: U$60.35, U$61.14
unnamed: U$60.36, U$61.13
unnamed: U$60.37, U$61.12
unnamed: U$60.38, U$61.11
unnamed: U$60.39, U$61.10
unnamed: U$60.40, U$61.9
unnamed: U$60.41, U$61.8
unnamed: U$60.42, U$61.7
unnamed: U$60.43, U$61.6
unnamed: U$60.44, U$61.5
unnamed: U$60.45, U$61.4
unnamed: U$60.46, U$61.3
unnamed: U$60.47, U$61.2
unnamed: U$60.48, U$61.1
unnamed: U$61.25, U$62.24
unnamed: U$61.26, U$62.23
unnamed: U$61.27, U$62.22
unnamed: U$61.28, U$62.21
unnamed: U$61.29, U$62.20
unnamed: U$61.30, U$62.19
unnamed: U$61.31, U$62.18
unnamed: U$61.32, U$62.17
unnamed: U$61.33, U$62.16
unnamed: U$61.34, U$62.15
unnamed: U$61.35, U$62.14
unnamed: U$61.36, U$62.13
unnamed: U$61.37, U$62.12
unnamed: U$61.38, U$62.11
unnamed: U$61.39, U$62.10
unnamed: U$61.40, U$62.9
unnamed: U$61.41, U$62.8
unnamed: U$61.42, U$62.7
unnamed: U$61.43, U$62.6
unnamed: U$61.44, U$62.5
unnamed: U$61.45, U$62.4
unnamed: U$61.46, U$62.3
unnamed: U$61.47, U$62.2
unnamed: U$61.48, U$62.1
unnamed: U$62.25, U$63.24
unnamed: U$62.26, U$63.23
unnamed: U$62.27, U$63.22
unnamed: U$62.28, U$63.21
unnamed: U$62.29, U$63.20
unnamed: U$62.30, U$63.19
unnamed: U$62.31, U$63.18
unnamed: U$62.32, U$63.17
unnamed: U$62.33, U$63.16
unnamed: U$62.34, U$63.15
unnamed: U$62.35, U$63.14
unnamed: U$62.36, U$63.13
unnamed: U$62.37, U$63.12
unnamed: U$62.38, U$63.11
unnamed: U$62.39, U$63.10
unnamed: U$62.40, U$63.9
unnamed: U$62.41, U$63.8
unnamed: U$62.42, U$63.7
unnamed: U$62.43, U$63.6
unnamed: U$62.44, U$63.5
unnamed: U$62.45, U$63.4
unnamed: U$62.46, U$63.3
unnamed: U$62.47, U$63.2
unnamed: U$62.48, U$63.1
unnamed: R14.1, U$7.A0, U$8.WDI
unnamed: BMS-OK.A, IC4.6, IC4.7
unnamed: BMS-OK.C, R15.1
unnamed: ON-LED.C, R16.1
unnamed: U$73.1, U$75.D3(CANTX)
unnamed: R30.2, U$73.8
unnamed: C9.2, R28.1
unnamed: C10.2, R29.1
unnamed: R31.1, TEENSY.C
unnamed: R33.1, U$74.16
unnamed: R33.2, R34.1, U$74.15
unnamed: C11.1, U$77.P$11
unnamed: U$73.4, U$75.D4(CANRX)
unnamed: TEENSY.A, U$75.D7(RX3)
unnamed: R38.2, U$76.WDO, U$78.2
unnamed: U$75.A1, U$78.1
unnamed: R42.1, U$75.A0, U$76.WDI
unnamed: BMS-OK2.A, IC6.6, IC6.7
unnamed: BMS-OK2.C, R17.1
unnamed: ON-LED2.C, R18.1
unnamed: U$79.1, U$81.D3(CANTX)
unnamed: R22.2, U$79.8
unnamed: C14.2, R20.1
unnamed: C17.2, R21.1
unnamed: R23.1, TEENSY2.C
unnamed: R24.1, U$80.16
unnamed: R24.2, R25.1, U$80.15
unnamed: C18.1, U$83.P$11
unnamed: U$79.4, U$81.D4(CANRX)
unnamed: TEENSY2.A, U$81.D7(RX3)
unnamed: R41.2, U$82.WDO, U$84.2
unnamed: U$81.A1, U$84.1
unnamed: R44.1, U$81.A0, U$82.WDI
unnamed: Q1.3, X3.2
unnamed: LED1.A, R49.1
unnamed: LED2.A, R50.2
unnamed: R51.2, U$87.1
unnamed: R50.1, U$85.D8(TX3)
unnamed: R49.2, U$85.D11
unnamed: J1.1, R46.2
unnamed: U$87.3, X4.1
unnamed: U$88.S2, X2.2
unnamed: U$88.S1, X2.1
unnamed: U$92.S2, X9.2
unnamed: U$92.S1, X9.1
unnamed: BMS-OK3.A, IC8.6, IC8.7
unnamed: BMS-OK3.C, R58.1
unnamed: ON-LED3.C, R59.1
unnamed: U$93.1, U$95.D3(CANTX)
unnamed: R63.2, U$93.8
unnamed: C27.2, R61.1
unnamed: C28.2, R62.1
unnamed: R64.1, TEENSY3.C
unnamed: R65.1, U$94.16
unnamed: R65.2, R66.1, U$94.15
unnamed: C29.1, U$97.P$11
unnamed: U$93.4, U$95.D4(CANRX)
unnamed: TEENSY3.A, U$95.D7(RX3)
unnamed: R69.2, U$96.WDO, U$98.2
unnamed: U$95.A1, U$98.1
unnamed: R71.1, U$95.A0, U$96.WDI
unnamed: Q3.3, X12.2
unnamed: LED4.A, R74.1
unnamed: LED5.A, R75.2
unnamed: R76.2, U$101.1
unnamed: R75.1, U$99.D8(TX3)
unnamed: R74.2, U$99.D11
unnamed: J3.1, R45.2
unnamed: U$101.3, X13.1
SCK_TEENSY: U$74.4, U$75.D13
SCK_TEENSY1: U$3.4, U$7.D13
SCK_TEENSY2: U$80.4, U$81.D13
SCK_TEENSY3: U$94.4, U$95.D13
SIGNAL_SAFE1: Q1.1, R47.1, R48.2, U$85.A0
SIGNAL_SAFE2: Q3.1, R72.1, R73.2, U$99.A0
